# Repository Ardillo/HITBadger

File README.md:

##The Hack In The Box (HITB) 2014 Amsterdam Badge
Also known as: <i>"HITBadger"</i> --> http://www.randomdata.nl/wiki/index.php/HITBadger <br>

Based on an arduino UNO with ATmega328.<br>
Goal is to have only through hole components so everybody can make one.<br>

We've used schematics from the Arduino Uno from Aruino.cc, 
Diavolino by Evil Mad Science and BoArduino by Adafruit.

We changed some default settings in the MIRF library to fit our needs.
Therefor we call it "HITBmirf" for example it uses 32 byte payloads as default.<br>
The NRF24L01+ could also used with the RF24 library from maniacbug and the standard MIRF 
library Look here for a good tutorial:<br>
http://maniacbug.wordpress.com/2011/11/02/getting-started-rf24/ <br>
His github can be cloned and used directly after copying the files to the
correct directory in your arduino installation.
https://github.com/maniacbug/RF24/ <br>

Build working concept with the "GettingStarted" program. I measured the power
consumption at 4.7V. it was 23mA. 
This could be enhanced by using a different library which puts the Arduino to
sleep, see: http://www.openhomeautomation.net/arduino-battery/ <br>
The power circuit seemed quite stable.

The HITBadger.zip contains all necessary Gerber files, 10 in total. 
Smart-prototyping needs 10 files, no offset, no mirror, no rotate, no upside
down. (http://smart-prototyping.com/PCB-Prototyping.html) <br>

##Arduino IDE
The board is completely programmable within the Arduino IDE. Therefor you need to copy the files 
of the <i>libraries</i> and <i>hardware</i> folder to the according folder of the Arduino IDE install folder.
The location of those folder varies depending on the OS you're using. A quick search on the internetzz will give 
you more information.
###Examples
We've included all the used programs during the event in the examples of our HITBmirf library, when 
imported correctly you can access them through the menu of your Arduino IDE.
A short explanation for the programs used in the event:
* HITBadgeClient <br>
The program everyone got on their personal badge with their nickname acting as a address.
* HITBadgeCommStation<br>
The program used on the base stations which where sending messages to the personal badges.
* HITBadgeCommSend -Receive <br>
Some testing code
* HITBadgeComStationParty<br>
The program used on the base stations during the after party to send everyone a message.
* HITBadgeLEDRoutine
A +/- 70 seconds during program which do all kinds of animations with the LED's.

###Hardware
Some of you have a ATmega328 and others have a ATmega328p both of the chips have the same pinout, but
when flashing a new bootloader (if you ever going to do so) you need some changements in your IDE.
If you copy the files of the <i> hardware</i> folder to the according location of your IDE you will notice
that two new options are available in the boards menu of the Arduino IDE. (Tools -> Board).
One of them is specific for uploading a new Arduino bootloader to a HITBadge with a ATmega328 (without the p).

##FTDI without DTR line
To use a FTDI uploader without a DTR line add a line to your preferences.txt of your Arduino IDE
<br>
<code>
upload.verbose = true
</code><br>
When the main init is started while uploading your code press the reset button to start the
bootloader of the Arduino again and upload your code. This takes some practice.
source: https://electronics.stackexchange.com/questions/2512/ftdi-basic-breakout-5v
<br>

Some url's to get you going:<br>
* https://learn.sparkfun.com/tutorials/how-to-install-and-setup-eagle/download-install-run<br>
* https://learn.sparkfun.com/tutorials/using-eagle-schematic/<br>
* https://learn.sparkfun.com/tutorials/using-eagle-board-layout/<br>
* https://learn.sparkfun.com/tutorials/making-custom-footprints-in-eagle/<br>
* https://learn.sparkfun.com/tutorials/designing-pcbs-smd-footprints/<br>
* http://arduino.cc/en/uploads/Hacking/Atmega168PinMap2.png<br>
* http://learn.adafruit.com/boarduino-kits<br>
* http://learn.adafruit.com/downloads/pdf/boarduino-kits.pdf<br>
* http://learn.adafruit.com/system/assets/assets/000/010/223/original/boarduinosch.png<br>
* https://www.adafruit.com/partfinder/<br>
* http://wiki.evilmadscientist.com/Diavolino<br>
* https://s3.amazonaws.com/evilmadscience/KitInstrux/diavolino_instrux.pdf<br>
* https://s3.amazonaws.com/evilmadscience/KitInstrux/diavolino_schematic.pdf<br>

####NRF24L01 specific URL's:
* http://arduino-info.wikispaces.com/Nrf24L01-2.4GHz-HowTo
* http://hack.lenotta.com/arduino-nrf24l01-modules-testing/
* http://maniacbug.wordpress.com/2011/11/02/getting-started-rf24/
* http://yourduino.com/docs/nRF24L01-Modules-connection-diagram.pdf
* http://playground.arduino.cc/InterfacingWithHardware/Nrf24L01

####Bill of "difficult" Materials (BOdM):
* http://nl.farnell.com/microchip/mcp1700-3302e-to/ic-v-reg-ldo-250ma-to-92-3/dp/1296588
* http://nl.farnell.com/microchip/mcp1702-5002e-to/ic-v-reg-ldo-250ma-to-92-3/dp/1331487
* http://nl.farnell.com/txc/9b-16-000meej-b/xtal-16-000mhz-18pf-hc-49s/dp/1842217<br>

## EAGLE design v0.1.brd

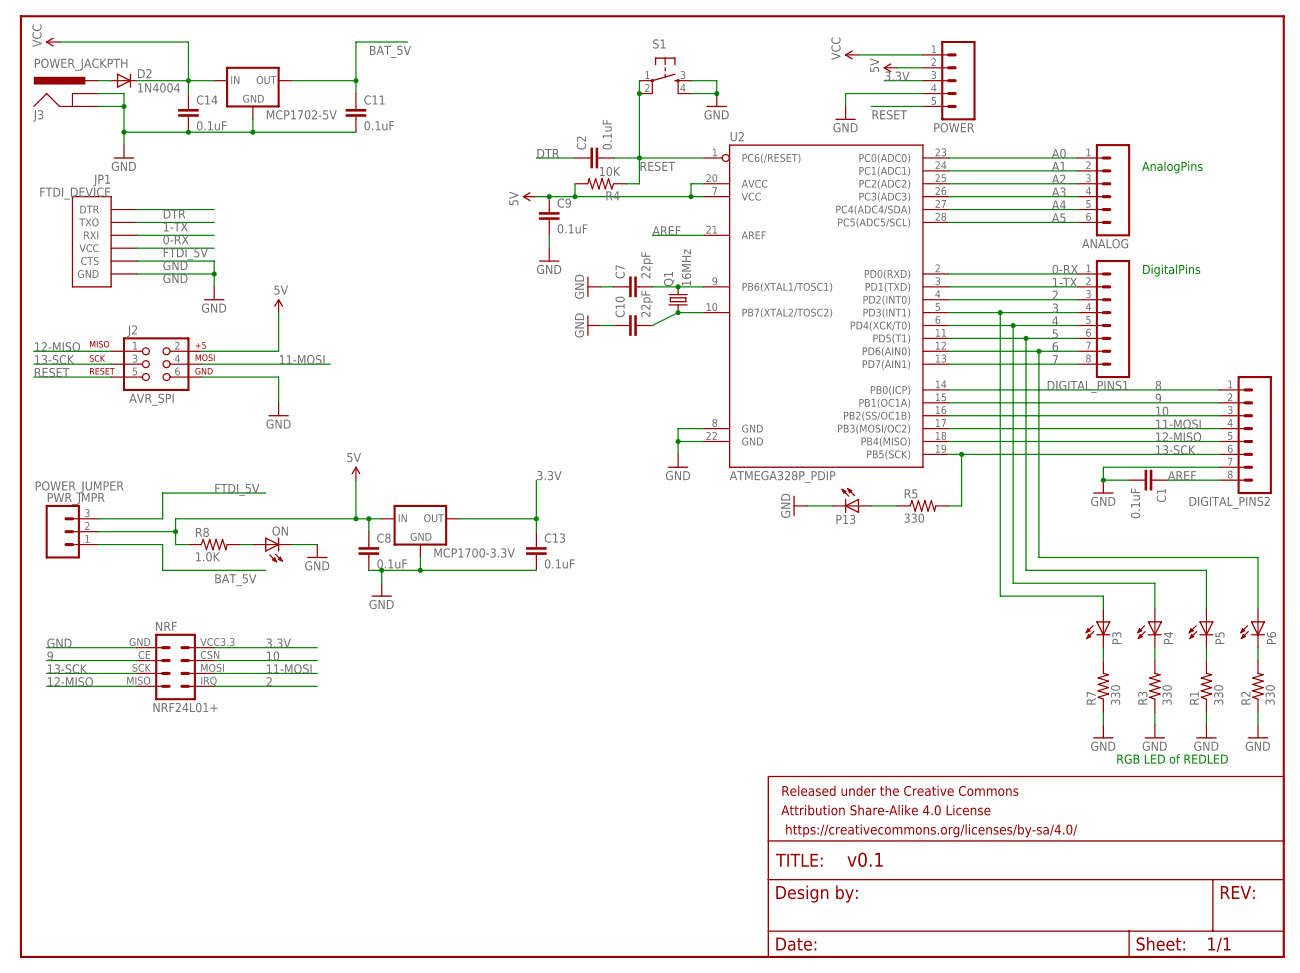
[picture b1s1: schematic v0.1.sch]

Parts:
ANALOG: M06LOCK; 1X06_LOCK
C1, C2, C8, C9, C11, C13, C14: 0.1uF; CAP-PTH-SMALL
C7, C10: 22pF; CAP-PTH-SMALL
D2: 1N4004; DO41-10
DIGITAL_PINS1, DIGITAL_PINS2: M08LOCK; 1X08_LOCK
FRAME1: FRAME-LETTER; CREATIVE_COMMONS
J2: AVR_SPI; 2X3
J3: POWER_JACKPTH; POWER_JACK_PTH
JP1: FTDI_DEVICE; FTDI_DEVICE_SIDE
MCP1700-3.3V, MCP1702-5V: MCP1700INLINE; TO92-INLINE
NRF: NRF24L01+; 2X4
ON: LED3MM
P3, P4, P5, P6: LED5MM
P13: LED3MM
POWER: M05LOCK; 1X05_LOCK
PWR_JMPR: M03LOCK; 1X03_LOCK
Q1: 16MHz; HC49/S
R1, R2, R3, R5, R7: 330; AXIAL-0.4
R4: 10K; AXIAL-0.4
R8: 1.0K; AXIAL-0.4
S1: TAC_SWITCHPTH; TACTILE-PTH
U2: ATMEGA328P_PDIP; DIL28-3

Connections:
0-RX: DIGITAL_PINS1.1, JP1.P$3 (RXI), U2.2 (PD0(RXD))
1-TX: DIGITAL_PINS1.2, JP1.P$2 (TXO), U2.3 (PD1(TXD))
2: DIGITAL_PINS1.3, NRF.IRQ, U2.4 (PD2(INT0))
3: DIGITAL_PINS1.4, P3.A, U2.5 (PD3(INT1))
3.3V: C13.1, MCP1700-3.3V.3 (OUT), NRF.VCC3.3 (VCC), POWER.3
4: DIGITAL_PINS1.5, P4.A, U2.6 (PD4(XCK/T0))
5: DIGITAL_PINS1.6, P5.A, U2.11 (PD5(T1))
5V: C8.1, C9.1, J2.2, MCP1700-3.3V.2 (IN), POWER.2, PWR_JMPR.2, R4.P$2 (2), R8.P$1 (1), U2.7 (VCC), U2.20 (AVCC)
6: DIGITAL_PINS1.7, P6.A, U2.12 (PD6(AIN0))
7: DIGITAL_PINS1.8, U2.13 (PD7(AIN1))
8: DIGITAL_PINS2.1, U2.14 (PB0(ICP))
9: DIGITAL_PINS2.2, NRF.CE, U2.15 (PB1(OC1A))
10: DIGITAL_PINS2.3, NRF.CSN, U2.16 (PB2(SS/OC1B))
11-MOSI: DIGITAL_PINS2.4, J2.4, NRF.MOSI, U2.17 (PB3(MOSI/OC2))
12-MISO: DIGITAL_PINS2.5, J2.1, NRF.MISO, U2.18 (PB4(MISO))
13-SCK: DIGITAL_PINS2.6, J2.3, NRF.SCK, R5.P$2 (2), U2.19 (PB5(SCK))
A0: ANALOG.1, U2.23 (PC0(ADC0))
A1: ANALOG.2, U2.24 (PC1(ADC1))
A2: ANALOG.3, U2.25 (PC2(ADC2))
A3: ANALOG.4, U2.26 (PC3(ADC3))
A4: ANALOG.5, U2.27 (PC4(ADC4/SDA))
A5: ANALOG.6, U2.28 (PC5(ADC5/SCL))
AREF: C1.1, DIGITAL_PINS2.8, U2.21 (AREF)
B: P5.K (C), R1.P$2 (2)
B1: P3.K (C), R7.P$2 (2)
BAT_5V: C11.1, MCP1702-5V.3 (OUT), PWR_JMPR.1
DTR: C2.1, JP1.P$1 (DTR)
FTDI_5V: JP1.P$4 (VCC), PWR_JMPR.3
GND: C1.2, C7.1, C8.2, C9.2, C10.1, C11.2, C13.2, C14.2, DIGITAL_PINS2.7, J2.6, J3.GND, J3.GNDBREAK, JP1.P$5 (CTS), JP1.P$6 (GND), MCP1700-3.3V.1 (GND), MCP1702-5V.1 (GND), NRF.GND, ON.K (C), P13.K (C), POWER.4, R1.P$1 (1), R2.P$1 (1), R3.P$1 (1), R7.P$1 (1), S1.3, S1.4, U2.8 (GND), U2.22 (GND)
unnamed: ON.A, R8.P$2 (2)
unnamed: P13.A, R5.P$1 (1)
unnamed: C10.2, Q1.1, U2.10 (PB7(XTAL2/TOSC2))
unnamed: C7.2, Q1.2, U2.9 (PB6(XTAL1/TOSC1))
unnamed: D2.A, J3.PWR
unnamed: P4.K (C), R3.P$2 (2)
unnamed: P6.K (C), R2.P$2 (2)
RESET: C2.2, J2.5, POWER.5, R4.P$1 (1), S1.1, S1.2, U2.1 (PC6(/RESET))
VCC: C14.1, D2.C, MCP1702-5V.2 (IN), POWER.1

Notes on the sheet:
RGB LED of REDLED
AnalogPins
DigitalPins

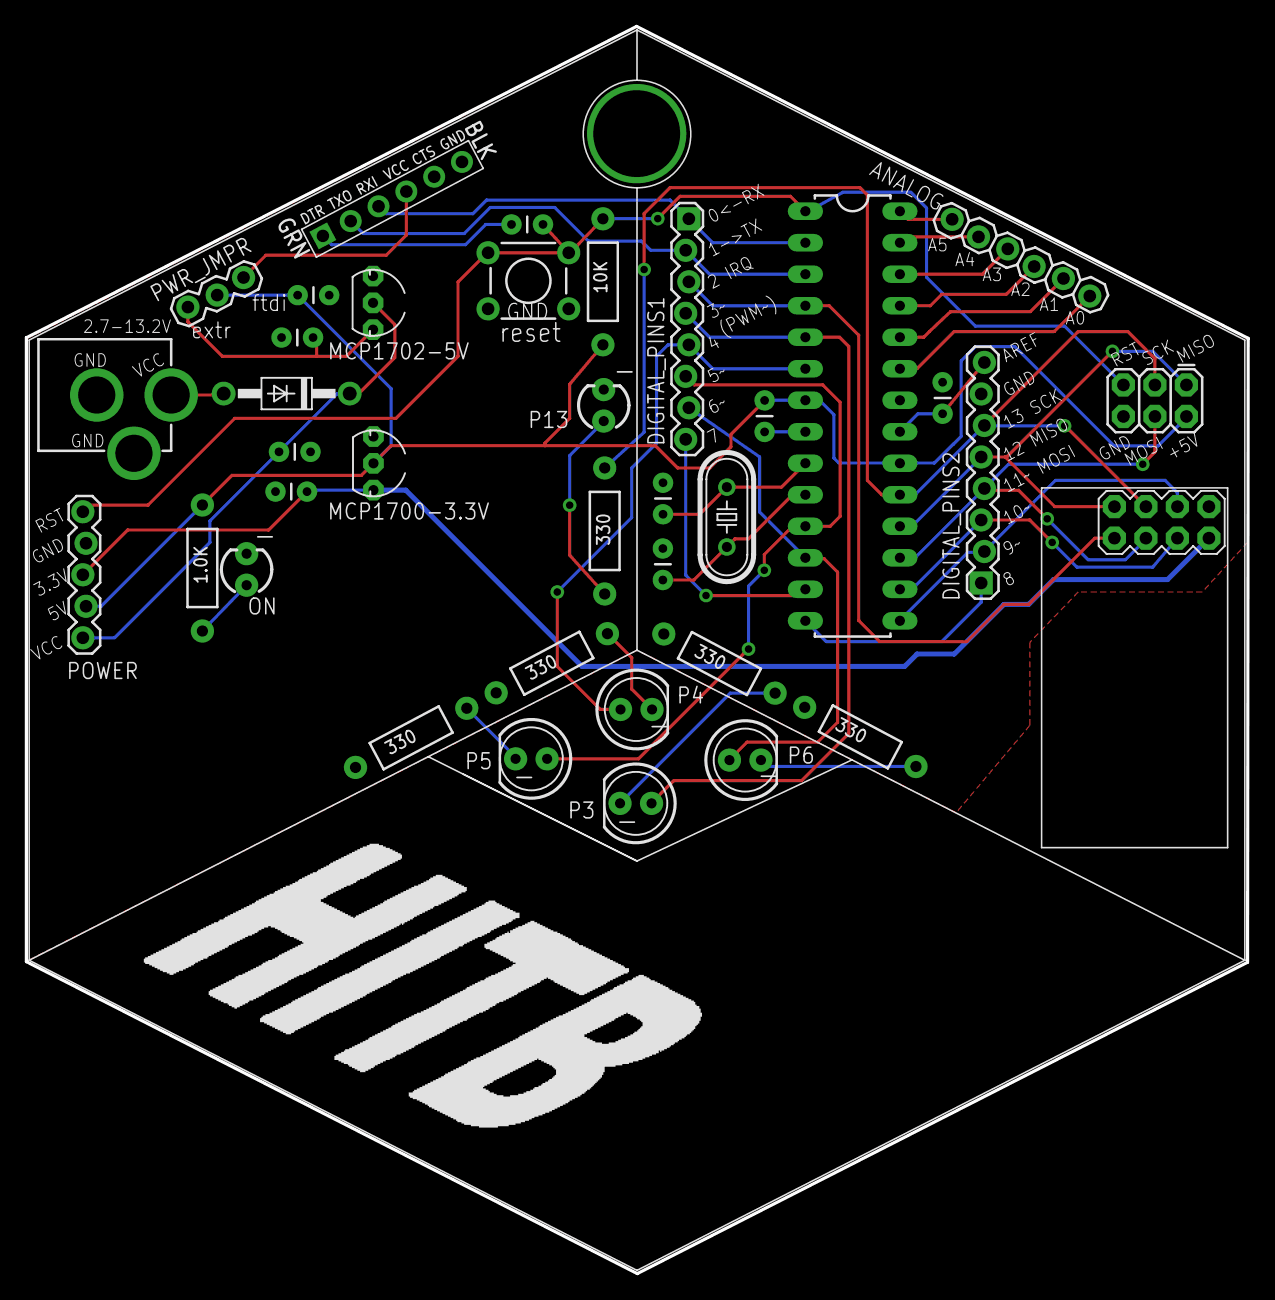
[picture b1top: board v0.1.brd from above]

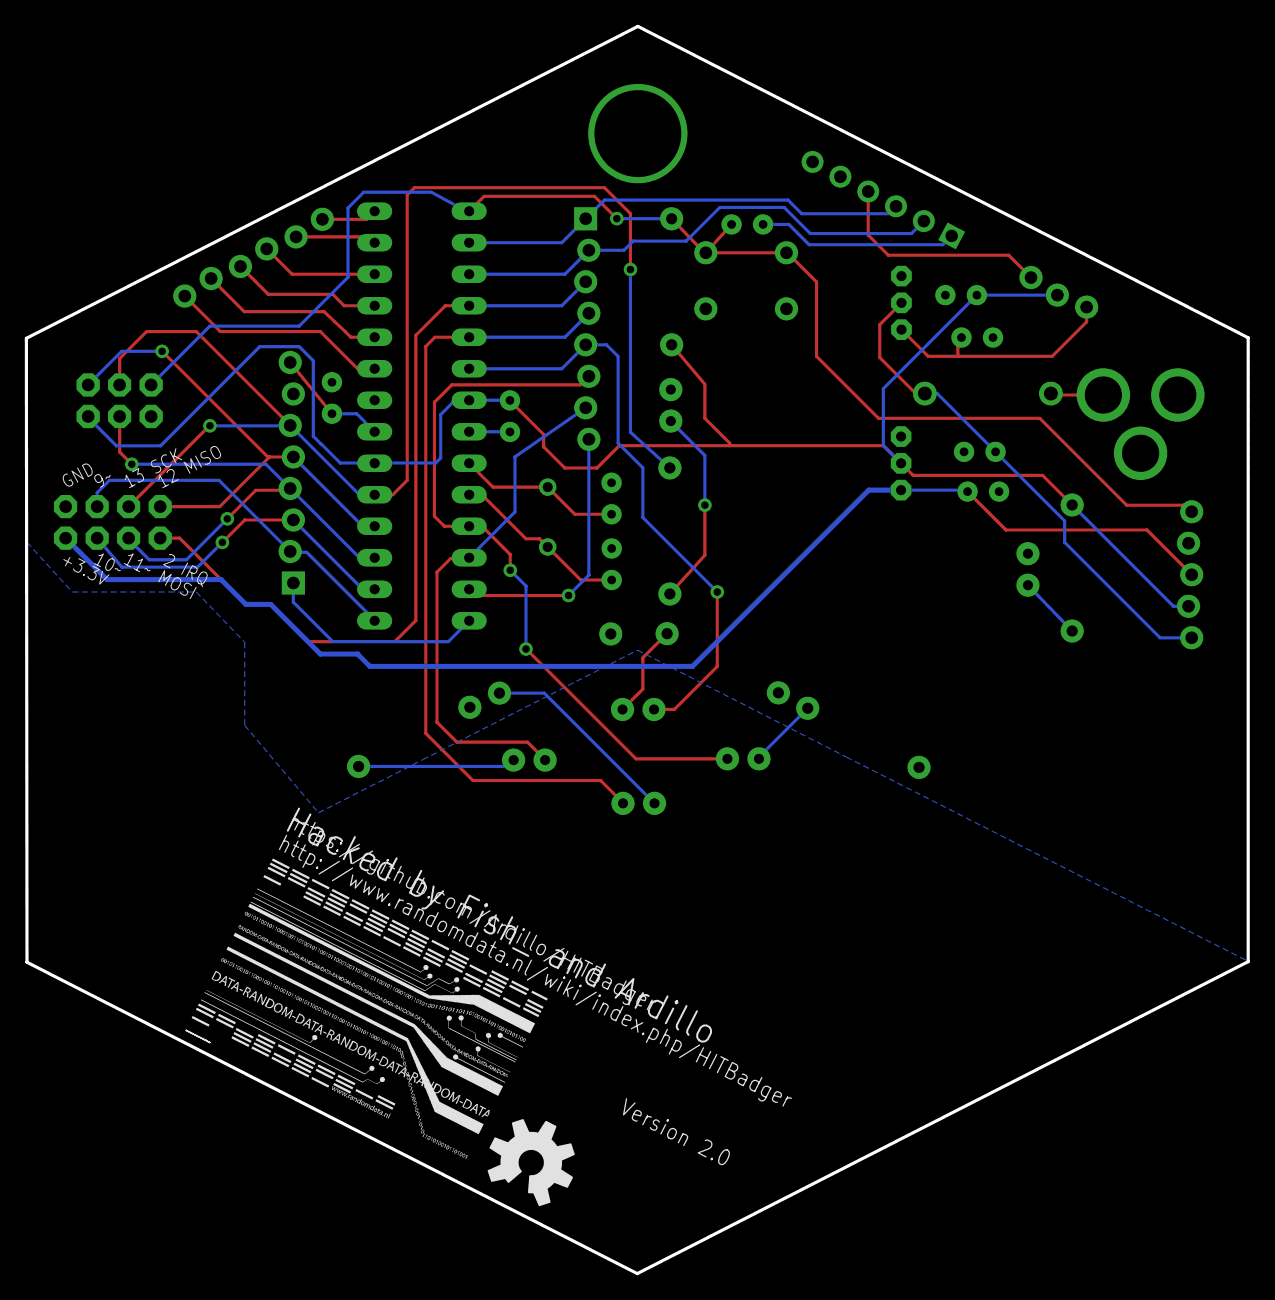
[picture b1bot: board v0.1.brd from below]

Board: 2 copper layers, 98.5 x 100.5 mm, 43 parts (3 on the bottom side), 38 nets.

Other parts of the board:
U$1: HITB_LOGO
U$2: HITB
U$3: OSHW-LOGO-L
U$4: OSHWLOGO_0.3
U$6: RANDOMDATA_LOGO_M

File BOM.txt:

Partlist exported from /home/ardillo/eagle/ownprojects/HITBadger/v0.1.sch at 3/24/14 9:44 PM

Part          Value           Device           Package          Description                                        MF MPN OC_FARNELL OC_NEWARK POWER_JUMPER PROD_ID  
ANALOG                        M06LOCK          1X06_LOCK        Header 6                                                                                             
C1            0.1uF           CAPPTH           CAP-PTH-SMALL    Capacitor                                                                                            
C2            0.1uF           CAPPTH           CAP-PTH-SMALL    Capacitor                                                                                            
C7            18pF            CAPPTH           CAP-PTH-SMALL    Capacitor                                                                                            
C8            0.1uF           CAPPTH           CAP-PTH-SMALL    Capacitor                                                                                            
C9            0.1uF           CAPPTH           CAP-PTH-SMALL    Capacitor                                                                                            
C10           18pF            CAPPTH           CAP-PTH-SMALL    Capacitor                                                                                            
C11           0.1uF           CAPPTH           CAP-PTH-SMALL    Capacitor                                                                                            
C13           0.1uF           CAPPTH           CAP-PTH-SMALL    Capacitor                                                                                            
C14           0.1uF           CAPPTH           CAP-PTH-SMALL    Capacitor                                                                                            
D2            1N4004          1N4004           DO41-10          DIODE                                                                                                
DIGITAL_PINS1                 M08LOCK          1X08_LOCK        Header 8                                                                                             
DIGITAL_PINS2                 M08LOCK          1X08_LOCK        Header 8                                                                                             
FRAME1        FRAME-LETTER    FRAME-LETTER     CREATIVE_COMMONS Schematic Frame                                                                                      
J2            AVR_SPI         AVR_SPI_PRG_6PTH 2X3              AVR ISP 6 Pin                                                                                        
J3            POWER_JACKPTH   POWER_JACKPTH    POWER_JACK_PTH   Power Jack                                                                                  PRT-00119
JP1           FTDI_DEVICE     FTDI_DEVICE      FTDI_DEVICE_SIDE Connector which mates to FTDI basic or FTDI cable.                                                   
MCP1700-3.3V                  MCP1700INLINE    TO92-INLINE      VOLTAGE REGULATOR                                                                                    
MCP1702-5V                    MCP1700INLINE    TO92-INLINE      VOLTAGE REGULATOR                                                                                    
NRF           NRF24L01+       NRF24L01+        2X4              .1" header, two rows of four.                                                                        
ON                            LED3MM           LED3MM           LEDs                                                                                                 
P3                            LED5MM           LED5MM           LEDs                                                                                                 
P5                            LED5MM           LED5MM           LEDs                                                                                                 
P6                            LED5MM           LED5MM           LEDs                                                                                                 
P9                            LED5MM           LED5MM           LEDs                                                                                                 
P13                           LED3MM           LED3MM           LEDs                                                                                                 
POWER                         M05LOCK          1X05_LOCK        Header 5                                                                                             
PWR_JMPR                      M03LOCK          1X03_LOCK        Header 3                                                                                             
Q1            16MHz           CRYSTALHC49S     HC49/S           CRYSTAL                                                   1667008    unknown                         
R1            330             RESISTORPTH-1/4W AXIAL-0.4        Resistor                                                                                             
R2            330             RESISTORPTH-1/4W AXIAL-0.4        Resistor                                                                                             
R3            330             RESISTORPTH-1/4W AXIAL-0.4        Resistor                                                                                             
R4            10K             RESISTORPTH-1/4W AXIAL-0.4        Resistor                                                                                             
R5            330             RESISTORPTH-1/4W AXIAL-0.4        Resistor                                                                                             
R7            330             RESISTORPTH-1/4W AXIAL-0.4        Resistor                                                                                             
R8            1.0K            RESISTORPTH-1/4W AXIAL-0.4        Resistor                                                                                             
S1                            TAC_SWITCHPTH    TACTILE-PTH      Momentary Switch                                                                                     
U2            ATMEGA328P_PDIP ATMEGA328P_PDIP  DIL28-3          uC used in the Arduino

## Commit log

2014-06-04 Update after event
2014-06-04 small change README
2014-06-04 small change
2015-05-28 Adding Arduino 1.5.1 and above support.
    As of 1.5.1 you have to define an upload tool. This was tested on 1.6.3.
2015-05-28 Fix buffer overflow
    This was causing a buffer overflow in line 138.
2015-05-28 Continuous mode client badge
    Slight change and cleanup to the client code. It will now run
    continuously until it gets a new update. You can still reset it to stop
    the current pattern.
2015-05-29 Arduino board manager install file
    This is needed for the arduino board manager.
2015-05-29 Json file for the Arduino Boards manager
    Needed for automated installation as of 1.6.4
2015-05-29 Let's try this again.
    Had to fix a few things.

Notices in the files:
parts and their libraries:
SparkFun-Capacitors: Licensing: Creative Commons ShareAlike 4.0 International - https://creativecommons.org/licenses/by-sa/4.0
SparkFun-Aesthetics: Released under the Creative Commons Attribution Share-Alike 4.0 License
SparkFun-Aesthetics: https://creativecommons.org/licenses/by-sa/4.0
